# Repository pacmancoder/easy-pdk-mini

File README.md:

# easy-pdk-mini

Easy PDK mini is the programmer hardware variant originated from
[easy-pdk-programmer-hardware](https://github.com/free-pdk/easy-pdk-programmer-hardware) project.

Schematics was simplified and the "lite" version of the programmer by *tim_* was used as a base for
this project, so in difference with the original hardware, this version works without MOSFET boost
converter enable switch and negative voltage charge pump for the opamp.

*Interactive BOM:* [link](http://pacmancoder.xyz/easy-pdk-mini/)

### Hand soldering
All passives have at least 0805 size, and the USB-B port was used instead of micro-USB, so it
should be easy to solder this programmer by the hand. The only quirky parts which may be
hard to solder is STM32 MCU and MT3608 boost converter. 

### Changes
Although existing "lite" version of easy-pdk-programmer (which was used as a reference for this
project) is relatively simple by itself, some additional simplifications was made:
- Removed 20Ohm USB series resistors. According to STM32F072 datasheet: *"No external termination
series resistors are required on USB_DP (D+) and USB_DM (D-); the matching impedance is already
included in the embedded driver"*
- Replaced boot button with simple jumper
- Replaced 47uF boost converter output capacitor with two 22uF caps to simplify process of finding
components (In my city I was not able to find 47uF 16v, while it was easy to find 22uF 25V)
- Added pull-down resistor for PB8 to make programmer detect as "lite" hardware
- Added 500mA 6v PTC fuse

### Schematics

### PCB

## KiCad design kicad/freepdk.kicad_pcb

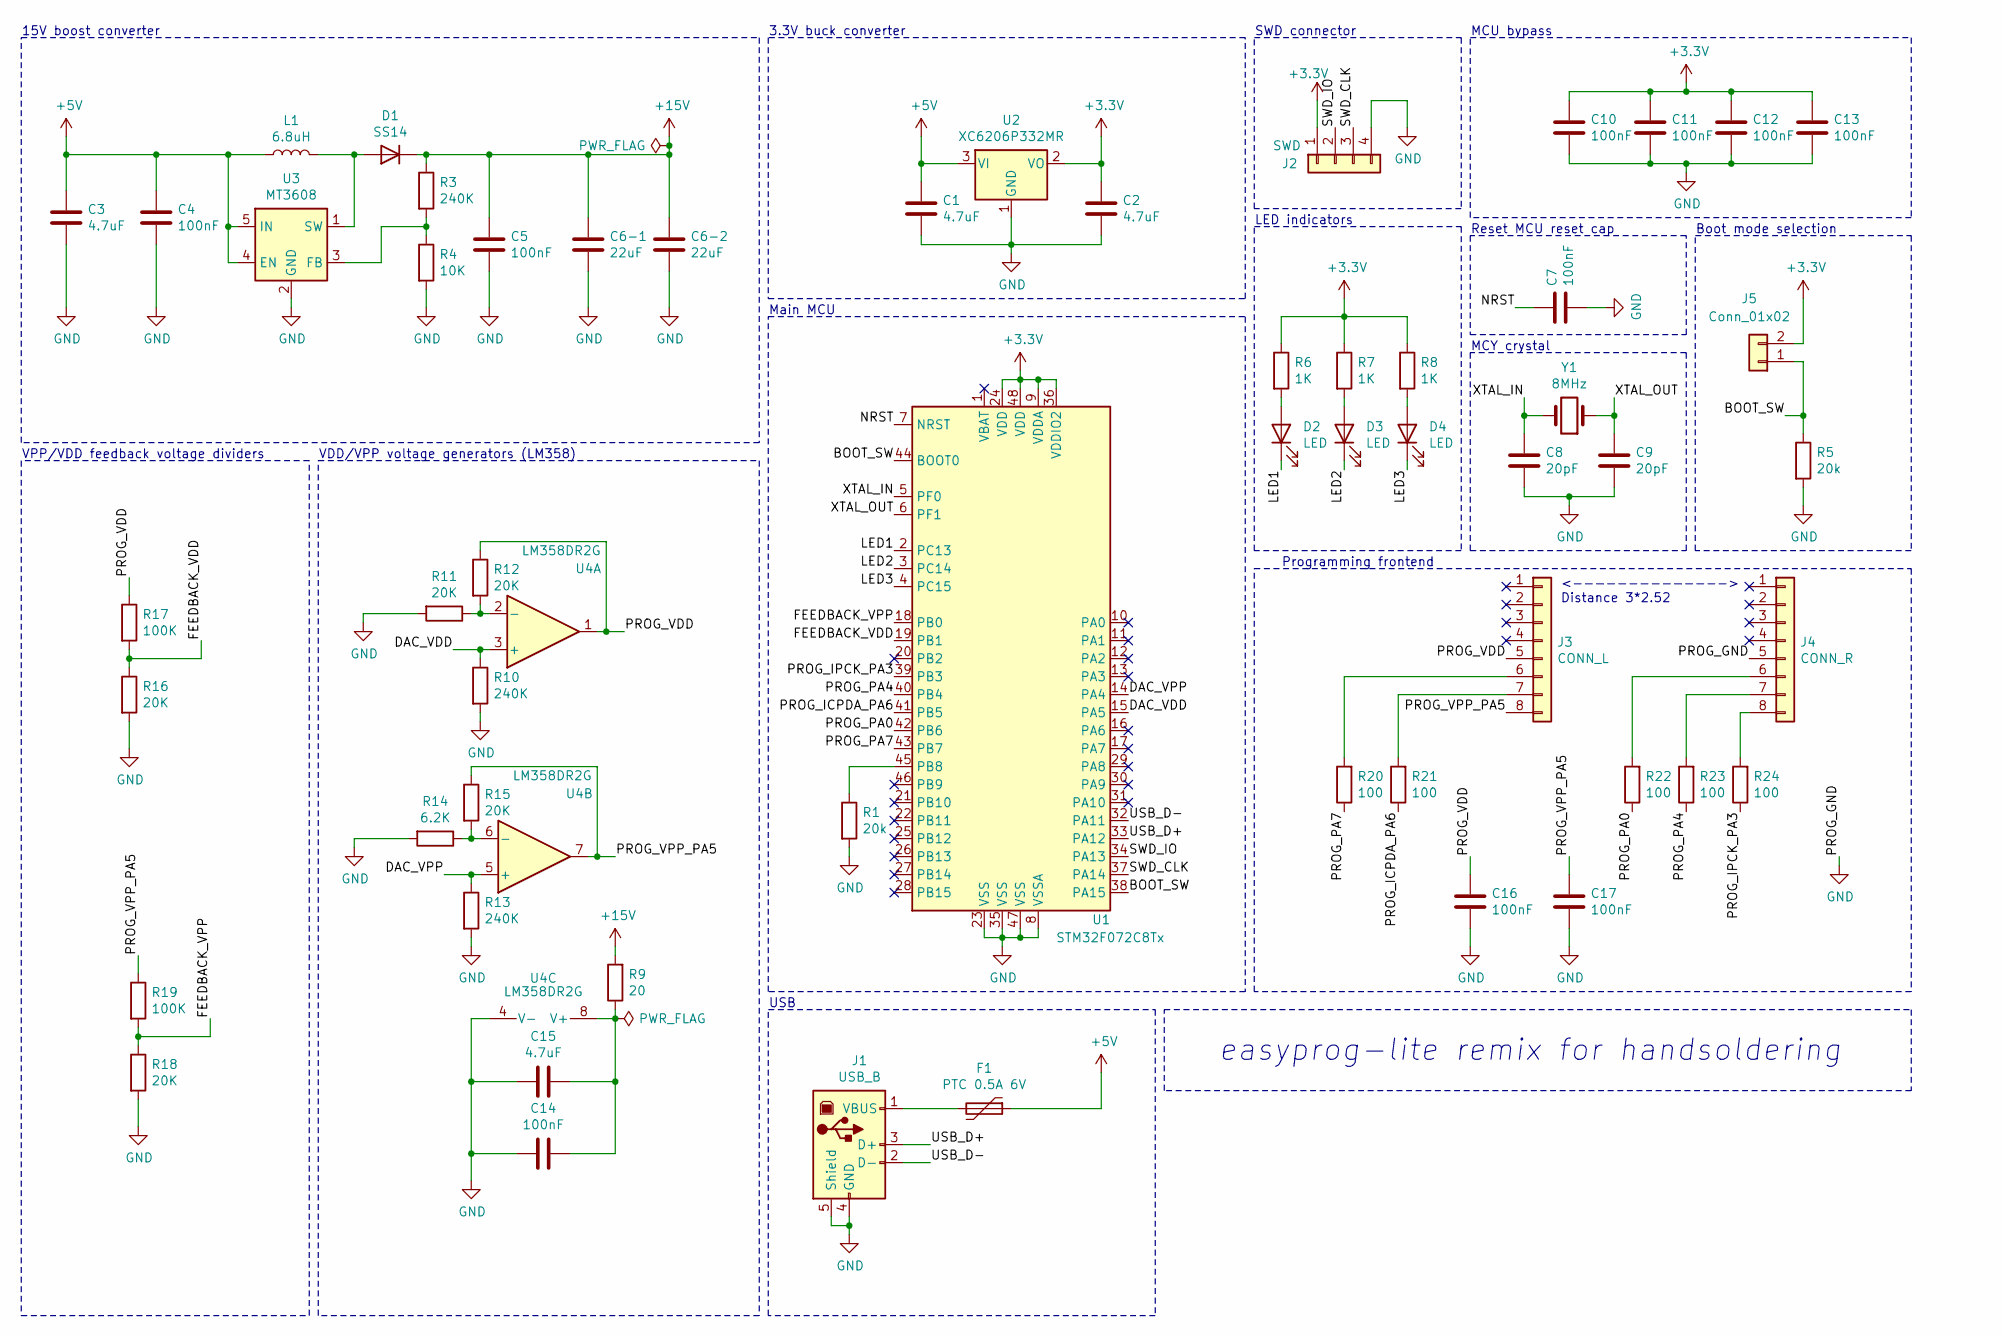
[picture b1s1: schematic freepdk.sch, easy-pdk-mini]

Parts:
C1, C2, C3, C15: 4.7uF; C_0805_2012Metric_Pad1.15x1.40mm_HandSolder
C4, C5, C7, C10, C11, C12, C13, C14, C16, C17: 100nF; C_0805_2012Metric_Pad1.15x1.40mm_HandSolder
C6-1, C6-2: 22uF; C_0805_2012Metric_Pad1.15x1.40mm_HandSolder
C8, C9: 20pF; C_0805_2012Metric_Pad1.15x1.40mm_HandSolder
D1: SS14; D_SMA_Handsoldering
D2, D3, D4: LED; LED_0805_2012Metric_Pad1.15x1.40mm_HandSolder
F1: PTC 0.5A 6V; Fuse_0805_2012Metric_Pad1.15x1.40mm_HandSolder
J1: USB_B; USB_B_OST_USB-B1HSxx_Horizontal
J2: SWD; PinHeader_1x04_P2.54mm_Vertical
J3: CONN_L; PinSocket_1x08_P2.54mm_Vertical
J4: CONN_R; PinSocket_1x08_P2.54mm_Vertical
J5: Conn_01x02; PinHeader_1x02_P2.54mm_Vertical
L1: 6.8uH; L_1210_3225Metric_Pad1.42x2.65mm_HandSolder
R1, R5: 20k; R_0805_2012Metric_Pad1.15x1.40mm_HandSolder
R3, R10, R13: 240K; R_0805_2012Metric_Pad1.15x1.40mm_HandSolder
R4: 10K; R_0805_2012Metric_Pad1.15x1.40mm_HandSolder
R6, R7, R8: 1K; R_0805_2012Metric_Pad1.15x1.40mm_HandSolder
R9: 20; R_0805_2012Metric_Pad1.15x1.40mm_HandSolder
R11, R12, R15, R16, R18: 20K; R_0805_2012Metric_Pad1.15x1.40mm_HandSolder
R14: 6.2K; R_0805_2012Metric_Pad1.15x1.40mm_HandSolder
R17, R19: 100K; R_0805_2012Metric_Pad1.15x1.40mm_HandSolder
R20, R21, R22, R23, R24: 100; R_0805_2012Metric_Pad1.15x1.40mm_HandSolder
U1: STM32F072C8Tx; LQFP-48_7x7mm_P0.5mm
U2: XC6206P332MR; SOT-23
U3: MT3608; SOT-23-6_Handsoldering
U4: LM358DR2G; SOIC-8_3.9x4.9mm_P1.27mm
Y1: 8MHz; Crystal_SMD_HC49-SD

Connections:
+3V3: C2.1, C10.1, C11.1, C12.1, C13.1, J2.1, J5.2, R6.1, R7.1, R8.1, U1.9 (VDDA), U1.24 (VDD), U1.36 (VDDIO2), U1.48 (VDD), U2.2 (VO)
+5V: C1.1, C3.1, C4.1, F1.1, L1.1, U2.3 (VI), U3.4 (EN), U3.5 (IN)
+15V: C5.1, C6-1.1, C6-2.1, D1.1 (K), R3.1, R9.2
/BOOT_SW: J5.1, R5.1, U1.38 (PA15), U1.44 (BOOT0)
/DAC_VDD: R10.1, U1.15 (PA5), U4.3 (+)
/DAC_VPP: R13.1, U1.14 (PA4), U4.5 (+)
/FEEDBACK_VDD: R16.1, R17.2, U1.19 (PB1)
/FEEDBACK_VPP: R18.1, R19.2, U1.18 (PB0)
/LED1: D2.1 (K), U1.2 (PC13)
/LED2: D3.1 (K), U1.3 (PC14)
/LED3: D4.1 (K), U1.4 (PC15)
/NRST: C7.1, U1.7 (NRST)
/PROG_ICPDA_PA6: R21.1, U1.41 (PB5)
/PROG_IPCK_PA3: R24.1, U1.39 (PB3)
/PROG_PA0: R22.1, U1.42 (PB6)
/PROG_PA4: R23.1, U1.40 (PB4)
/PROG_PA7: R20.1, U1.43 (PB7)
/PROG_VDD: C16.1, J3.5, R12.1, R17.1, U4.1
/PROG_VPP_PA5: C17.1, J3.8, R15.1, R19.1, U4.7
/SWD_CLK: J2.3, U1.37 (PA14)
/SWD_IO: J2.2, U1.34 (PA13)
/USB_D+: J1.3 (D+), U1.33 (PA12)
/USB_D-: J1.2 (D-), U1.32 (PA11)
/XTAL_IN: C8.2, U1.5 (PF0), Y1.2
/XTAL_OUT: C9.2, U1.6 (PF1), Y1.1
GND: C1.2, C2.2, C3.2, C4.2, C5.2, C6-1.2, C6-2.2, C7.2, C8.1, C9.1, C10.2, C11.2, C12.2, C13.2, C14.2, C15.2, C16.2, C17.2, J1.4 (GND), J1.5 (Shield), J2.4, J4.5, R1.2, R4.2, R5.2, R10.2, R11.2, R13.2, R14.2, R16.2, R18.2, U1.8 (VSSA), U1.23 (VSS), U1.35 (VSS), U1.47 (VSS), U2.1 (GND), U3.2 (GND), U4.4 (V-)
unnamed: C14.1, C15.1, R9.1, U4.8 (V+)
unnamed: D1.2 (A), L1.2, U3.1 (SW)
unnamed: D2.2 (A), R6.2
unnamed: D3.2 (A), R7.2
unnamed: D4.2 (A), R8.2
unnamed: F1.2, J1.1 (VBUS)
unnamed: J3.6, R20.2
unnamed: J3.7, R21.2
unnamed: J4.6, R22.2
unnamed: J4.7, R23.2
unnamed: J4.8, R24.2
unnamed: R1.1, U1.45 (PB8)
unnamed: R3.2, R4.1, U3.3 (FB)
unnamed: R11.1, R12.2, U4.2 (-)
unnamed: R14.1, R15.2, U4.6 (-)

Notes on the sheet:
SWD connector
Programming frontend
MCY crystal
MCU bypass
LED indicators
Reset MCU reset cap
Boot mode selection
3.3V buck converter
Main MCU
USB
VDD/VPP voltage generators (LM358)
VPP/VDD feedback voltage dividers
15V boost converter
easyprog-lite remix for handsoldering
<--------------> Distance 3*2.52

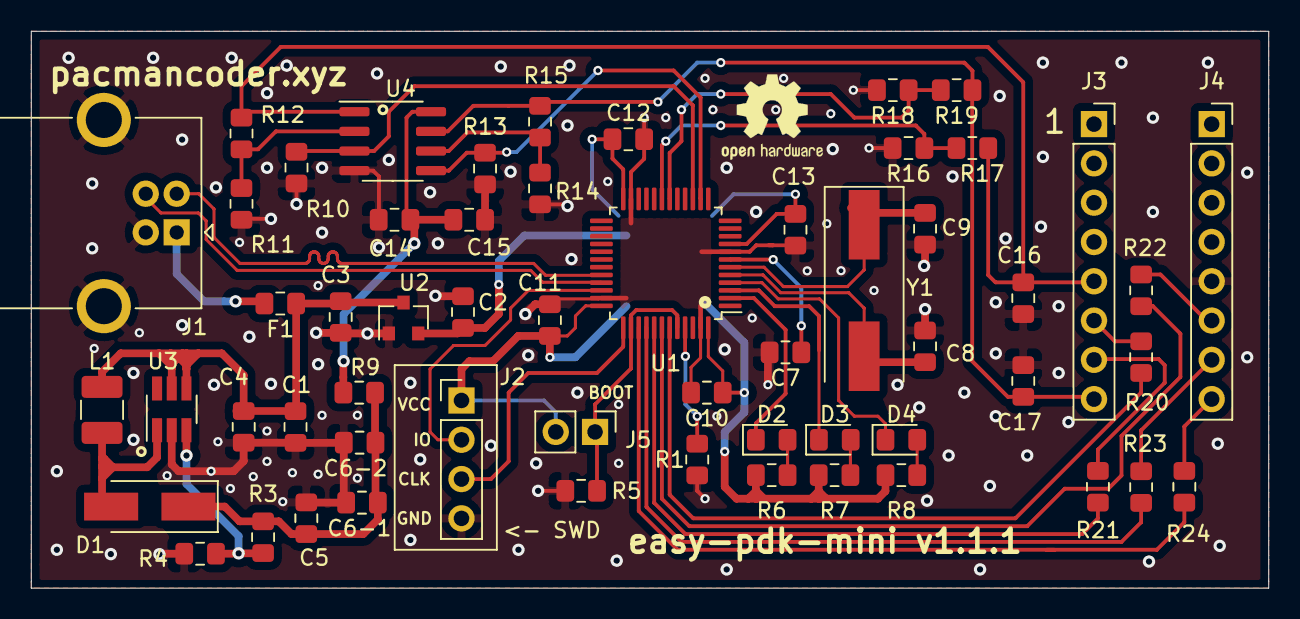
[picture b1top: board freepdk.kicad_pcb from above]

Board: 2 copper layers, 80.0 x 36.0 mm, 57 parts (0 on the bottom side), 41 nets.

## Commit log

2020-09-06 First revision
2020-09-06 Added warning about absence of testing
2020-09-07 Fixed formatting
2020-09-07 Second revision - Added fuse, improved routing, changed pcb dimentsions
2020-09-07 Fixed silkscreen and markings
2020-09-07 Added Interactive BOM
2020-09-08 Revision 3 - Applied suggestions from review, prepared gerbers
2020-09-08 Revision 3 patch: Replaced wrong opamp; Removed logo from BOM
2020-09-08 Fixed interactive BOM link
2020-09-19 Fixed issue with wrong opamp wiring
2020-09-23 Updated PCB to use USB-B port instead of Mini-usb
2020-09-23 Updated gerbers for v1.1.0
2020-09-23 Updated interactive BOM and updated gerbers after minor bugfixes
